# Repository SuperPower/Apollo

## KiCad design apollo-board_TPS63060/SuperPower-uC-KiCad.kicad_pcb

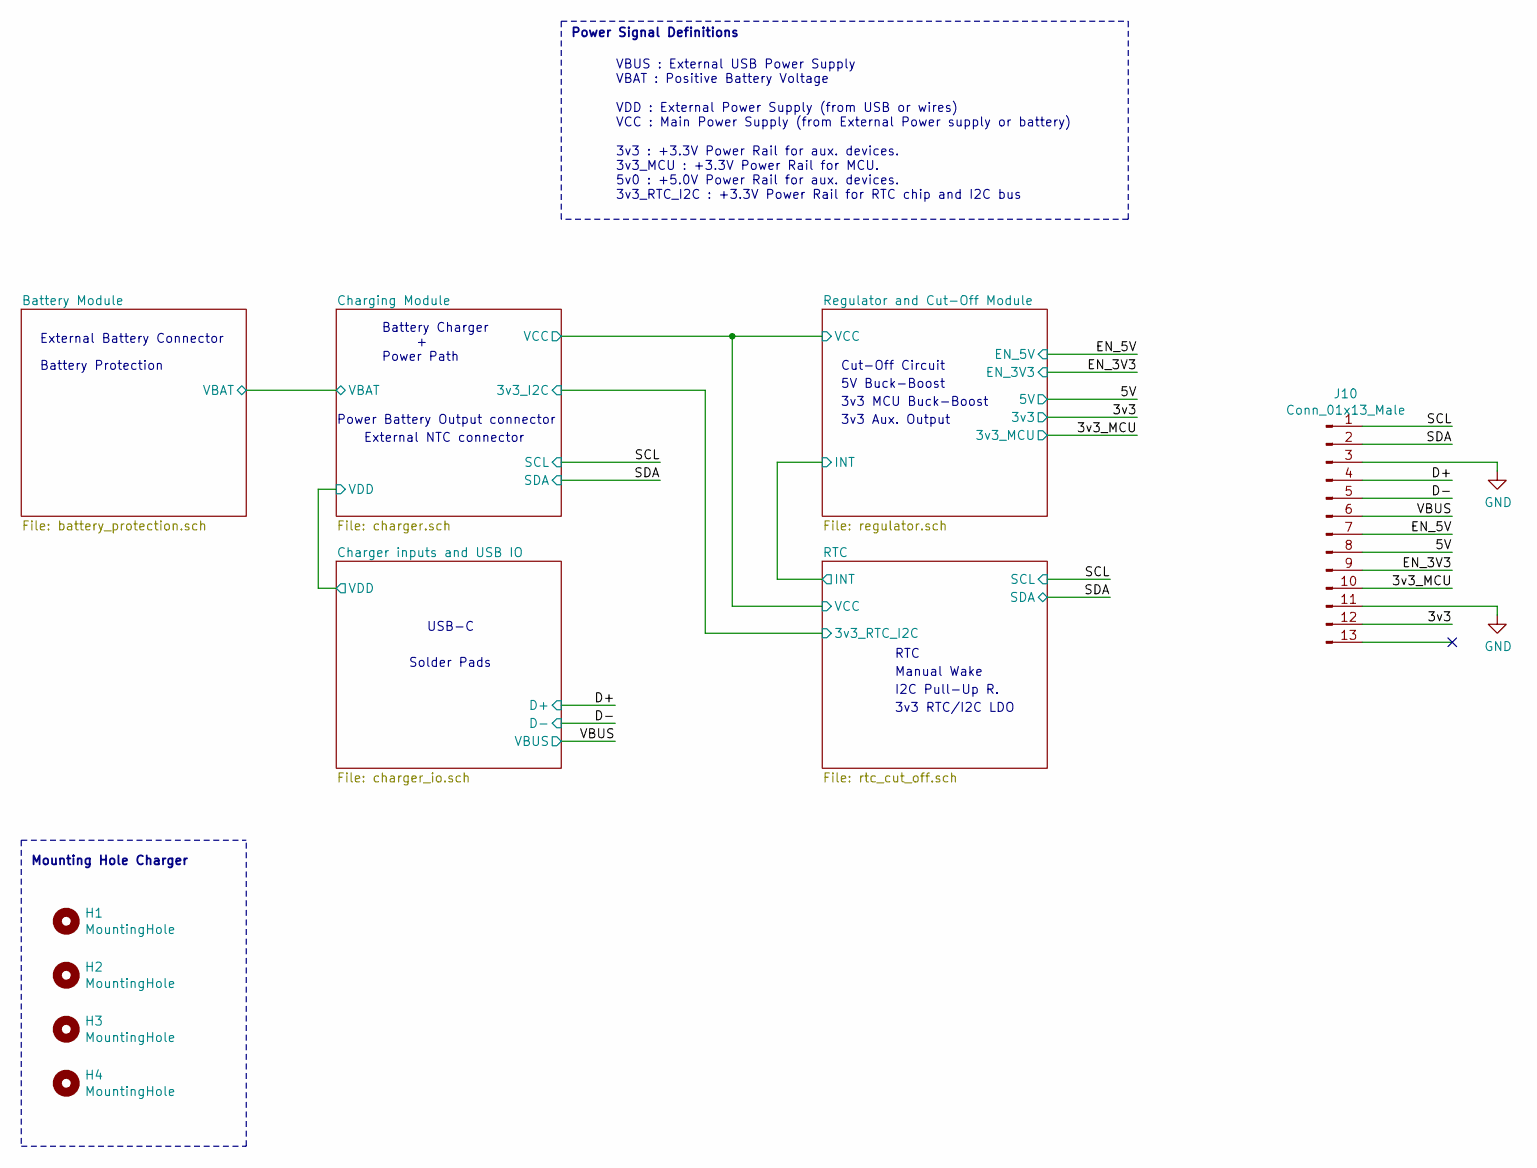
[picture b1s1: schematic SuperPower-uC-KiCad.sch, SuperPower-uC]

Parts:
H1, H2, H3, H4: MountingHole; MountingHole_2.5mm
J10: Conn_01x13_Male; PinSocket_1x13_P2.54mm_Vertical

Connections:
/3v3: J10.12; also elsewhere on the board
/3v3_MCU: J10.10; also elsewhere on the board
/5V: J10.8; also elsewhere on the board
/D+: J10.4; also elsewhere on the board
/D-: J10.5; also elsewhere on the board
/EN_3V3: J10.9; also elsewhere on the board
/EN_5V: J10.7; also elsewhere on the board
/SCL: J10.1; also elsewhere on the board
/SDA: J10.2; also elsewhere on the board
GND: J10.3, J10.11; also elsewhere on the board
VBUS: J10.6; also elsewhere on the board

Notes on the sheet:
External Battery Connector
Battery Protection
Battery Charger + Power Path
3v3 RTC/I2C LDO
3v3 MCU Buck-Boost
5V Buck-Boost
RTC
Cut-Off Circuit
USB-C
Solder Pads
Manual Wake
I2C Pull-Up R.
Mounting Hole Charger
Power Battery Output connector
External NTC connector
3v3 Aux. Output
VBUS : External USB Power Supply VBAT : Positive Battery Voltage VDD : External Power Supply (from USB or wires) VCC : Main Power Supply (from External Power supply or battery) 3v3 : +3.3V Power Rail for aux. devices. 3v3_MCU : +3.3V Power Rail for MCU. 5v0 : +5.0V Power Rail for aux. devices. 3v3_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
Power Signal Definitions

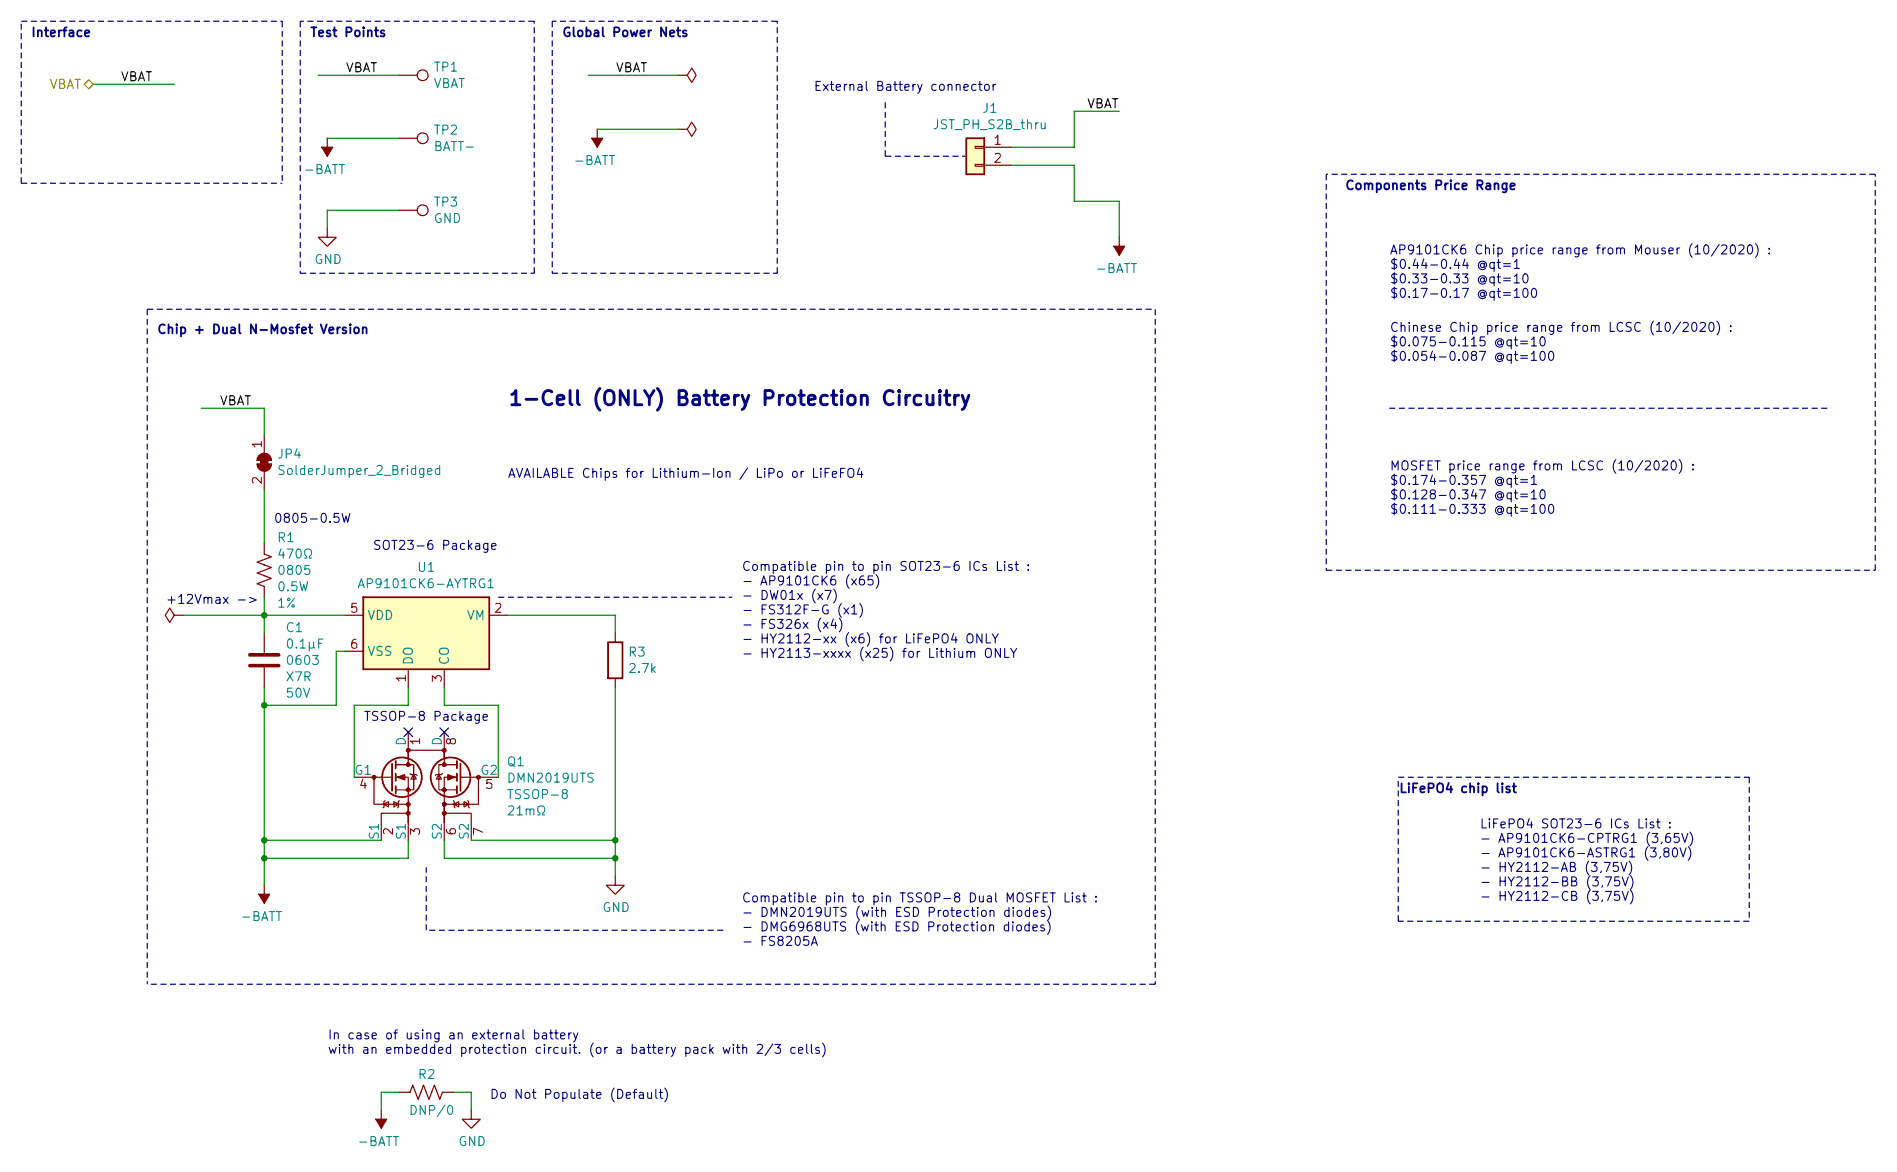
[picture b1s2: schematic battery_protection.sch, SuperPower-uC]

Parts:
C1: CC0603JRX7R9BB104; C_0603_1608Metric; Farnell_ref 3369214
J1: JST_PH_S2B_thru; JST_PH_S2B-PH-K_1x02_P2.00mm_Horizontal; Farnell_ref 9491902
JP4: SolderJumper_2_Bridged; SolderJumper-2_P1.3mm_Bridged_RoundedPad1.0x1.5mm
Q1: DMN2019UTS; TSSOP-8_4.4x3mm_P0.65mm; Farnell_check_date 2020-12-05
R1: ERJ-P06F4700V; R_0805_2012Metric; Farnell_check_date 2020-12-17
R2: DNP/0; R_0603_1608Metric
R3: 2.7k; R_0603_1608Metric
TP1: VBAT; TestPoint_Pad_D1.0mm
TP2: BATT-; TestPoint_Pad_D1.0mm
TP3: GND; TestPoint_Pad_D1.0mm
U1: AP9101CK6-AYTRG1; SOT-23-6; Farnell_check_date 2020-11-28

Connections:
-BATT: C1.2, J1.2, Q1.2 (S1), Q1.3 (S1), R2.2, TP2.1, U1.6 (VSS)
/Battery Module/VBAT: J1.1, JP4.1 (A), TP1.1; also elsewhere on the board
GND: Q1.6 (S2), Q1.7 (S2), R2.1, R3.2, TP3.1; also elsewhere on the board
unnamed: C1.1, R1.2, U1.5 (VDD)
unnamed: JP4.2 (B), R1.1
unnamed: Q1.4 (G1), U1.1 (DO)
unnamed: Q1.5 (G2), U1.3 (CO)
unnamed: R3.1, U1.2 (VM)

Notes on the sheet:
SOT23-6 Package
TSSOP-8 Package
Compatible pin to pin SOT23-6 ICs List : - AP9101CK6 (x65) - DW01x (x7) - FS312F-G (x1) - FS326x (x4) - HY2112-xx (x6) for LiFePO4 ONLY - HY2113-xxxx (x25) for Lithium ONLY
AVAILABLE Chips for Lithium-Ion / LiPo or LiFeFO4
AP9101CK6 Chip price range from Mouser (10/2020) : $0.44-0.44 @qt=1 $0.33-0.33 @qt=10 $0.17-0.17 @qt=100
Compatible pin to pin TSSOP-8 Dual MOSFET List : - DMN2019UTS (with ESD Protection diodes) - DMG6968UTS (with ESD Protection diodes) - FS8205A
MOSFET price range from LCSC (10/2020) : $0.174-0.357 @qt=1 $0.128-0.347 @qt=10 $0.111-0.333 @qt=100
LiFePO4 SOT23-6 ICs List : - AP9101CK6-CPTRG1 (3,65V) - AP9101CK6-ASTRG1 (3,80V) - HY2112-AB (3,75V) - HY2112-BB (3,75V) - HY2112-CB (3,75V)
Chinese Chip price range from LCSC (10/2020) : $0.075-0.115 @qt=10 $0.054-0.087 @qt=100
Chip + Dual N-Mosfet Version
LiFePO4 chip list
In case of using an external battery with an embedded protection circuit. (or a battery pack with 2/3 cells)
External Battery connector
Interface
Components Price Range
1-Cell (ONLY) Battery Protection Circuitry
+12Vmax ->
Do Not Populate (Default)
0805-0.5W
Test Points
Global Power Nets

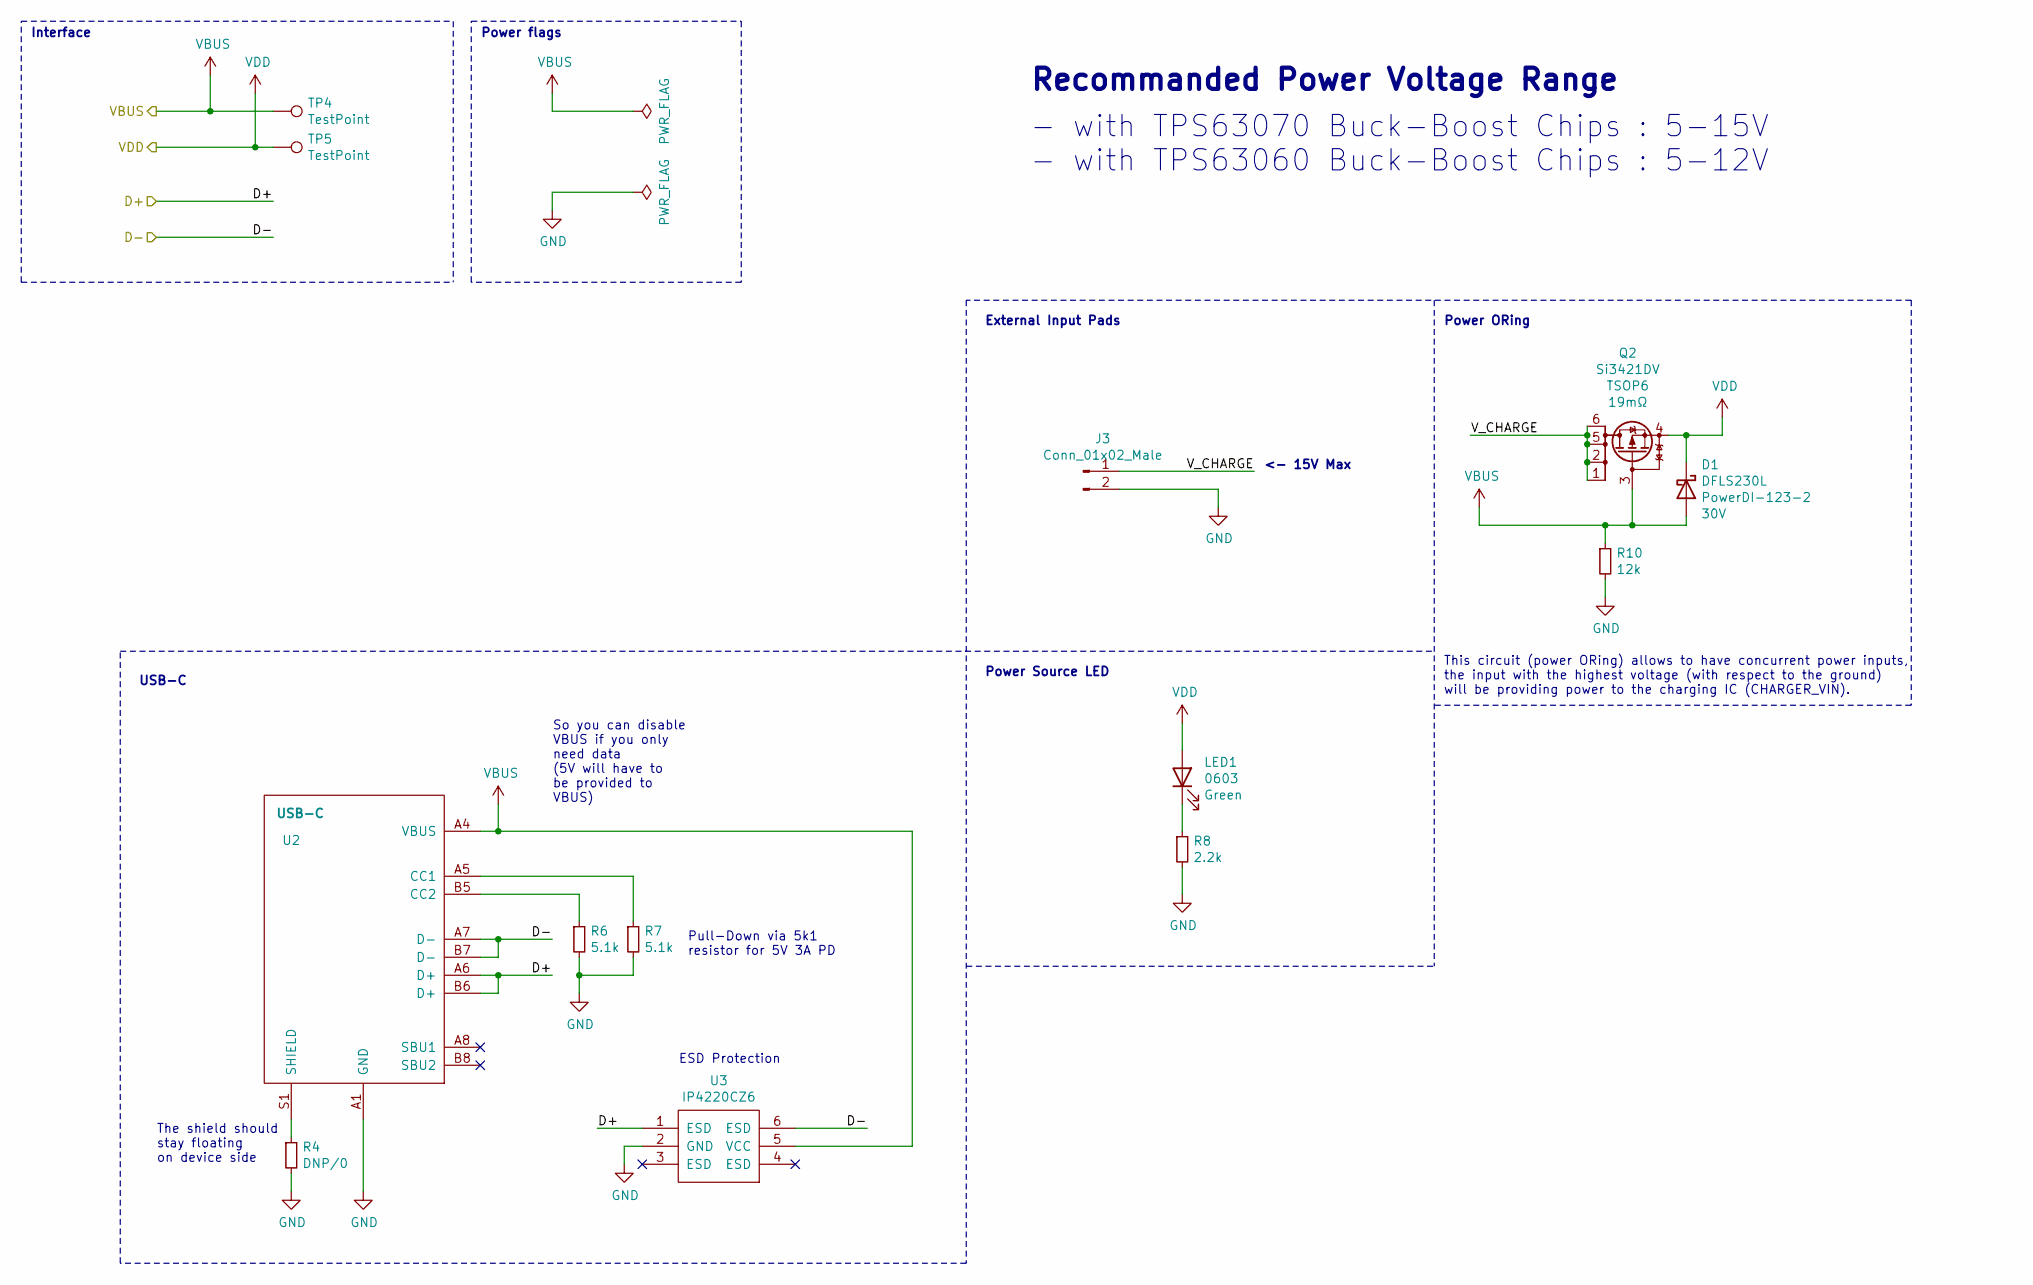
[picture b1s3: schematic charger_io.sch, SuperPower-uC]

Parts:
D1: DFLS230L; D_PowerDI-123; Farnell_ref 1858663
J3: Conn_01x02_Male; ext_input_pads
LED1: 150060VS75000_0603; LED_0603_1608Metric; Farnell_ref 2322073
Q2: Si3421DV; TSOP-6_1.65x3.05mm_P0.95mm; Farnell_ref 3405183
R4: DNP/0; R_0603_1608Metric
R6, R7: 5.1k; R_0603_1608Metric
R8: 2.2k; R_0603_1608Metric
R10: 12k; R_0603_1608Metric
TP4, TP5: TestPoint; TestPoint_Pad_D1.0mm
U2: USB-C; usb-c-usb4105
U3: IP4220CZ6; TSOP-6_1.65x3.05mm_P0.95mm

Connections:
/Charger inputs and USB IO/V_CHARGE: J3.1, Q2.1 (D), Q2.2 (D), Q2.5 (D), Q2.6 (D)
/D+: U2.A6 (D+), U2.B6 (D+), U3.1 (ESD); also elsewhere on the board
/D-: U2.A7 (D-), U2.B7 (D-), U3.6 (ESD); also elsewhere on the board
GND: J3.2, R4.2, R6.2, R7.2, R8.2, R10.2, U2.A1 (GND), U2.A12 (GND), U2.B1 (GND), U2.B12 (GND), U3.2 (GND); also elsewhere on the board
unnamed: LED1.1 (K), R8.1
unnamed: R4.1, U2.S1 (SHIELD)
unnamed: R6.1, U2.B5 (CC2)
unnamed: R7.1, U2.A5 (CC1)
VBUS: D1.2 (A), Q2.3 (G), R10.1, TP4.1, U2.A4 (VBUS), U2.A9 (VBUS), U2.B4 (VBUS), U2.B9 (VBUS), U3.5 (VCC); also elsewhere on the board
VDD: D1.1 (K), LED1.2 (A), Q2.4 (S), TP5.1; also elsewhere on the board

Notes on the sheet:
Pull-Down via 5k1 resistor for 5V 3A PD
External Input Pads
USB-C
So you can disable VBUS if you only need data (5V will have to be provided to VBUS)
ESD Protection
The shield should stay floating on device side
Power ORing
This circuit (power ORing) allows to have concurrent power inputs, the input with the highest voltage (with respect to the ground) will be providing power to the charging IC (CHARGER_VIN).
Power Source LED
Interface
Recommanded Power Voltage Range
<- 15V Max
Power flags
- with TPS63070 Buck-Boost Chips : 5-15V - with TPS63060 Buck-Boost Chips : 5-12V

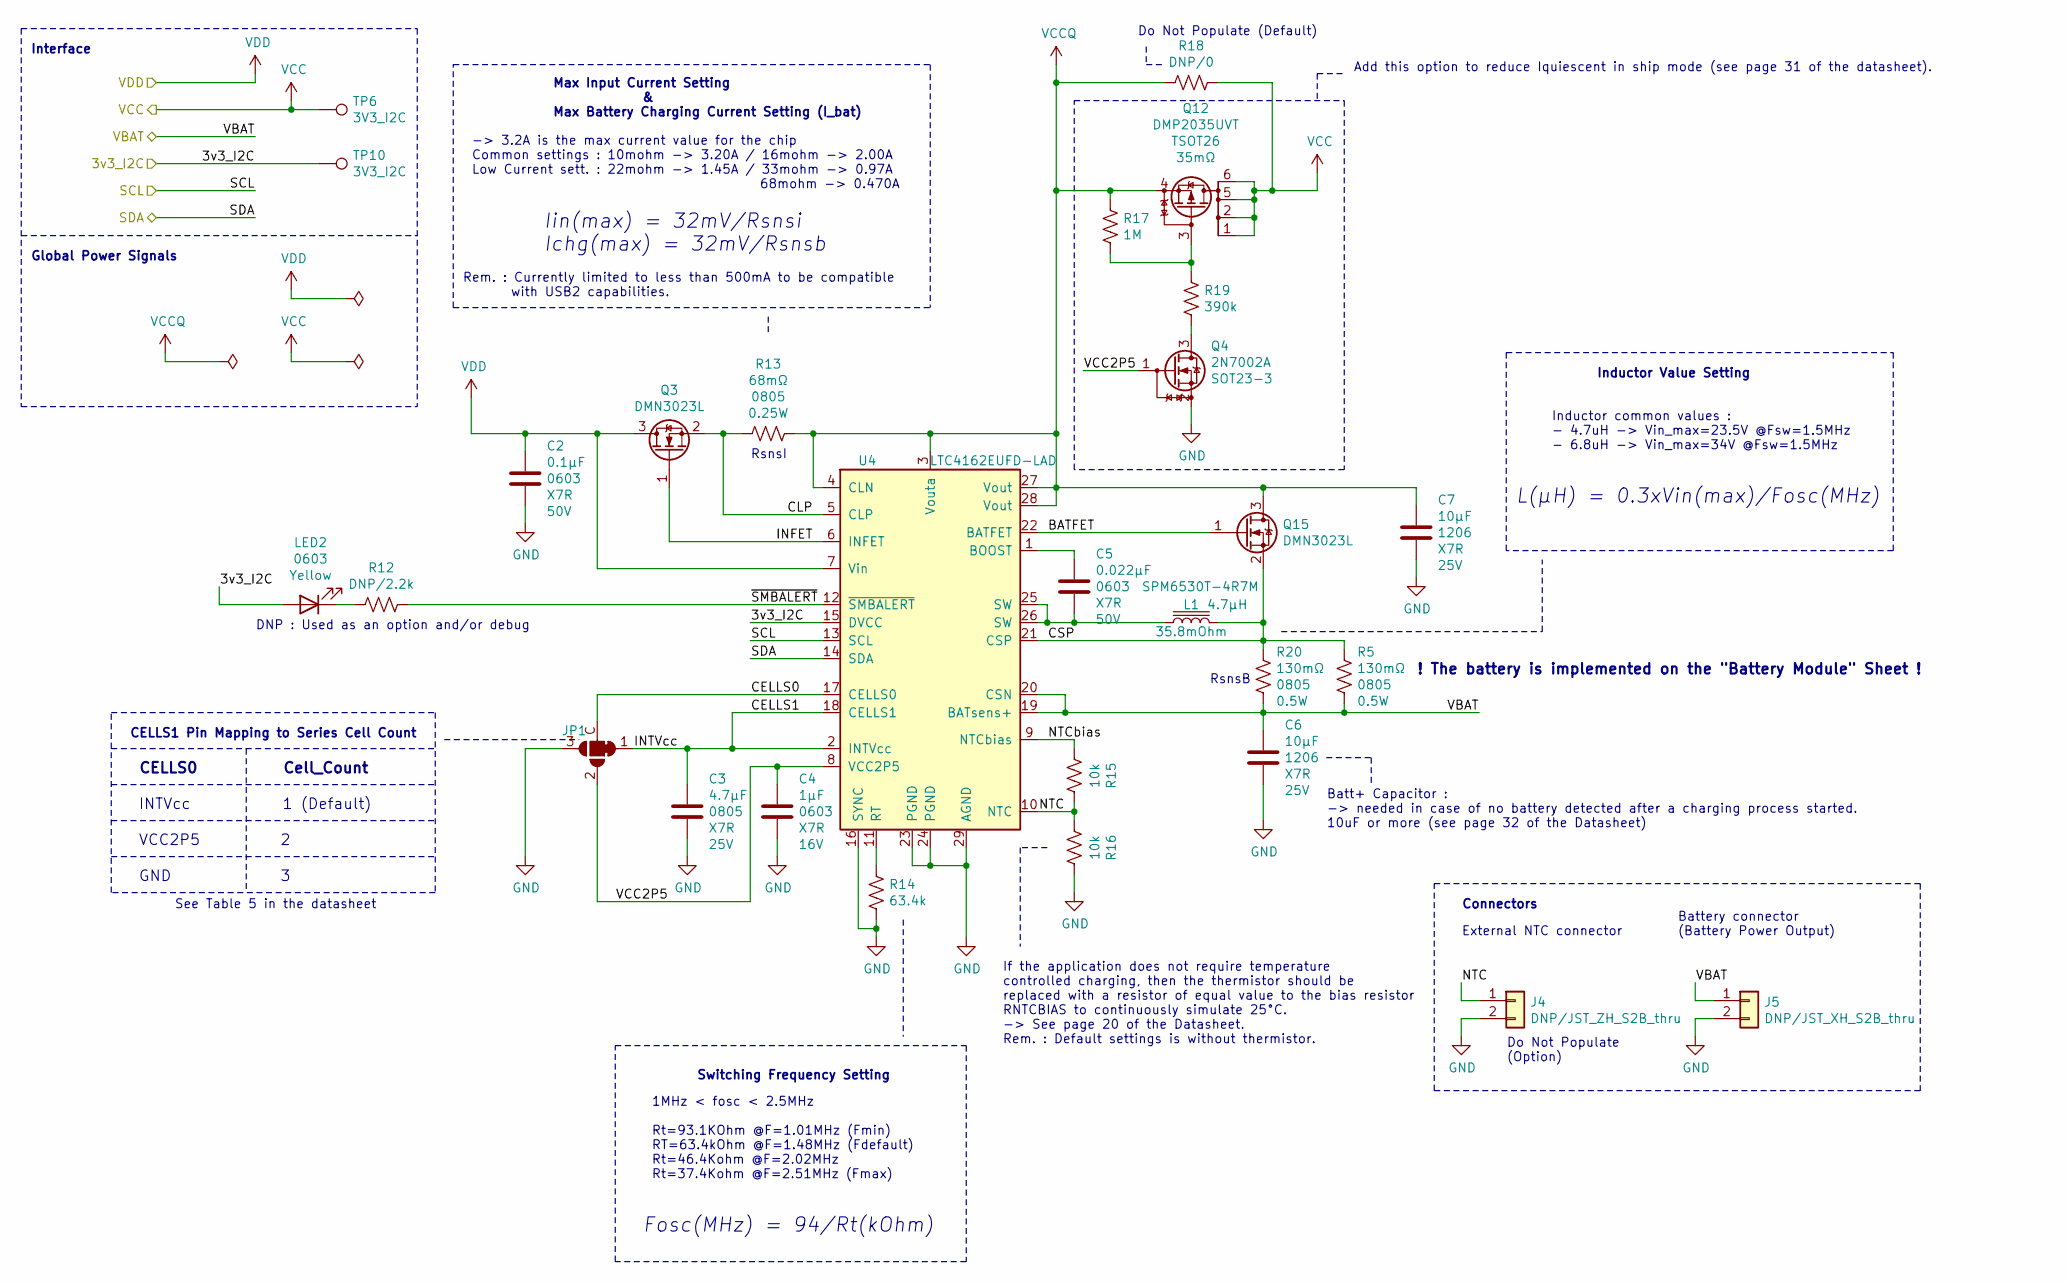
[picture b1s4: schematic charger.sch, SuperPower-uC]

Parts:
C2: CC0603JRX7R9BB104; C_0603_1608Metric; Farnell_ref 3369214
C3: TMK212AB7475KG-T; C_0805_2012Metric; Farnell_ref 2779199
C4: CL10B105KO8NNNC; C_0603_1608Metric; Farnell_ref 3013416
C5: CL10B223KB8NNNC; C_0603_1608Metric; Farnell_ref 3013425
C6, C7: CL31B106KAHNNNE; C_1206_3216Metric; Farnell_ref 3013526
J4: DNP/JST_ZH_S2B_thru; PinHeader_1x02_P1.27mm_Vertical; Farnell_ref 9491813
J5: DNP/JST_XH_S2B_thru; PinHeader_1x02_P2.54mm_Vertical; Farnell_ref 1516289
JP1: SolderJumper_4_Bridged_1C; SolderJumper-4_P2.0mm_Bridged1C_TrianglePad1.0x1.5mm_Number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
L1: SPM6530T-4R7M; L_TDK_SPM6530T; LCSC_ref C76857
LED2: 150060YS75000_0603; LED_0603_1608Metric; Farnell_ref 2322074
Q3, Q15: DMN3023L; SOT-23
Q4: 2N7002A; SOT-23; Farnell_ref 3127180
Q12: DMP2035UVT; SOT-23-6; Farnell_ref 3405183
R5, R20: ERJ-6DSFR13V; R_0805_2012Metric; Farnell_check_date 2021-08-02
R12: DNP/2.2k; R_0603_1608Metric
R13: RL0805FR-7W0R068L; R_0805_2012Metric; Farnell_ref 8067694
R14: 63.4k; R_0603_1608Metric
R15, R16: 10k; R_0603_1608Metric
R17: 1M; R_0603_1608Metric
R18: DNP/0; R_0603_1608Metric
R19: 390k; R_0603_1608Metric
TP6, TP10: 3V3_I2C; TestPoint_Pad_D1.0mm
U4: LTC4162EUFD-LAD; QFN-28-1EP_4x5mm_P0.5mm_EP2.65x3.65mm_ThermalVias; Farnell_check_date 2020-11-22

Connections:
/Battery Module/VBAT: C6.1, J5.1, R5.2, R20.2, U4.19 (BATsens+), U4.20 (CSN); also elsewhere on the board
/Charging Module/3v3_I2C: LED2.2 (A), TP10.1, U4.15 (DVCC); also elsewhere on the board
/Charging Module/BATFET: Q15.1 (G), U4.22 (BATFET)
/Charging Module/CELLS0: JP1.C (Com), U4.17 (CELLS0)
/Charging Module/CELLS1: C3.1, JP1.1 (A), U4.2 (INTVcc), U4.18 (CELLS1)
/Charging Module/CLP: Q3.2 (S), R13.2, U4.5 (CLP)
/Charging Module/CSP: L1.2, Q15.2 (S), R5.1, R20.1, U4.21 (CSP)
/Charging Module/INFET: Q3.1 (G), U4.6 (INFET)
/Charging Module/NTC: J4.1, R15.1, R16.2, U4.10 (NTC)
/Charging Module/NTCbias: R15.2, U4.9 (NTCbias)
/Charging Module/VCC2P5: C4.1, JP1.2 (B), Q4.1 (G), U4.8 (VCC2P5)
/Charging Module/~SMBALERT: R12.1, U4.12 (~SMBALERT)
/SCL: U4.13 (SCL); also elsewhere on the board
/SDA: U4.14 (SDA); also elsewhere on the board
GND: C2.2, C3.2, C4.2, C6.2, C7.2, J4.2, J5.2, JP1.3 (C), Q4.2 (S), R14.1, R16.1, U4.16 (SYNC), U4.23 (PGND), U4.24 (PGND), U4.29 (AGND); also elsewhere on the board
unnamed: C5.1, U4.1 (BOOST)
unnamed: C5.2, L1.1, U4.25 (SW), U4.26 (SW)
unnamed: LED2.1 (K), R12.2
unnamed: Q4.3 (D), R19.2
unnamed: Q12.3 (G), R17.2, R19.1
unnamed: R14.2, U4.11 (RT)
VCC: Q12.1 (D), Q12.2 (D), Q12.5 (D), Q12.6 (D), R18.1, TP6.1; also elsewhere on the board
VCCQ: C7.1, Q12.4 (S), Q15.3 (D), R13.1, R17.1, R18.2, U4.3 (Vouta), U4.4 (CLN), U4.27 (Vout), U4.28 (Vout)
VDD: C2.1, Q3.3 (D), U4.7 (Vin); also elsewhere on the board

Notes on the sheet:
RsnsB
RsnsI
If the application does not require temperature controlled charging, then the thermistor should be replaced with a resistor of equal value to the bias resistor RNTCBIAS to continuously simulate 25°C. -> See page 20 of the Datasheet. Rem. : Default settings is without thermistor.
Batt+ Capacitor : -> needed in case of no battery detected after a charging process started. 10uF or more (see page 32 of the Datasheet)
1MHz < fosc < 2.5MHz Rt=93.1KOhm @F=1.01MHz (Fmin) RT=63.4kOhm @F=1.48MHz (Fdefault) Rt=46.4Kohm @F=2.02MHz Rt=37.4Kohm @F=2.51MHz (Fmax)
Inductor common values : - 4.7uH -> Vin_max=23.5V @Fsw=1.5MHz - 6.8uH -> Vin_max=34V @Fsw=1.5MHz
Add this option to reduce Iquiescent in ship mode (see page 31 of the datasheet).
External NTC connector
Switching Frequency Setting
Max Input Current Setting & Max Battery Charging Current Setting (I_bat)
-> 3.2A is the max current value for the chip Common settings : 10mohm -> 3.20A / 16mohm -> 2.00A Low Current sett. : 22mohm -> 1.45A / 33mohm -> 0.97A 68mohm -> 0.470A
Inductor Value Setting
Battery connector (Battery Power Output)
DNP : Used as an option and/or debug
See Table 5 in the datasheet
Connectors
! The battery is implemented on the "Battery Module" Sheet !
Iin(max) = 32mV/Rsnsi Ichg(max) = 32mV/Rsnsb
Fosc(MHz) = 94/Rt(kOhm)
L(µH) = 0.3xVin(max)/Fosc(MHz)
CELLS1 Pin Mapping to Series Cell Count
CELLS0
Cell_Count
INTVcc
VCC2P5
GND
1 (Default)
Rem. : Currently limited to less than 500mA to be compatible with USB2 capabilities.
Interface
Do Not Populate (Option)
Do Not Populate (Default)
Global Power Signals

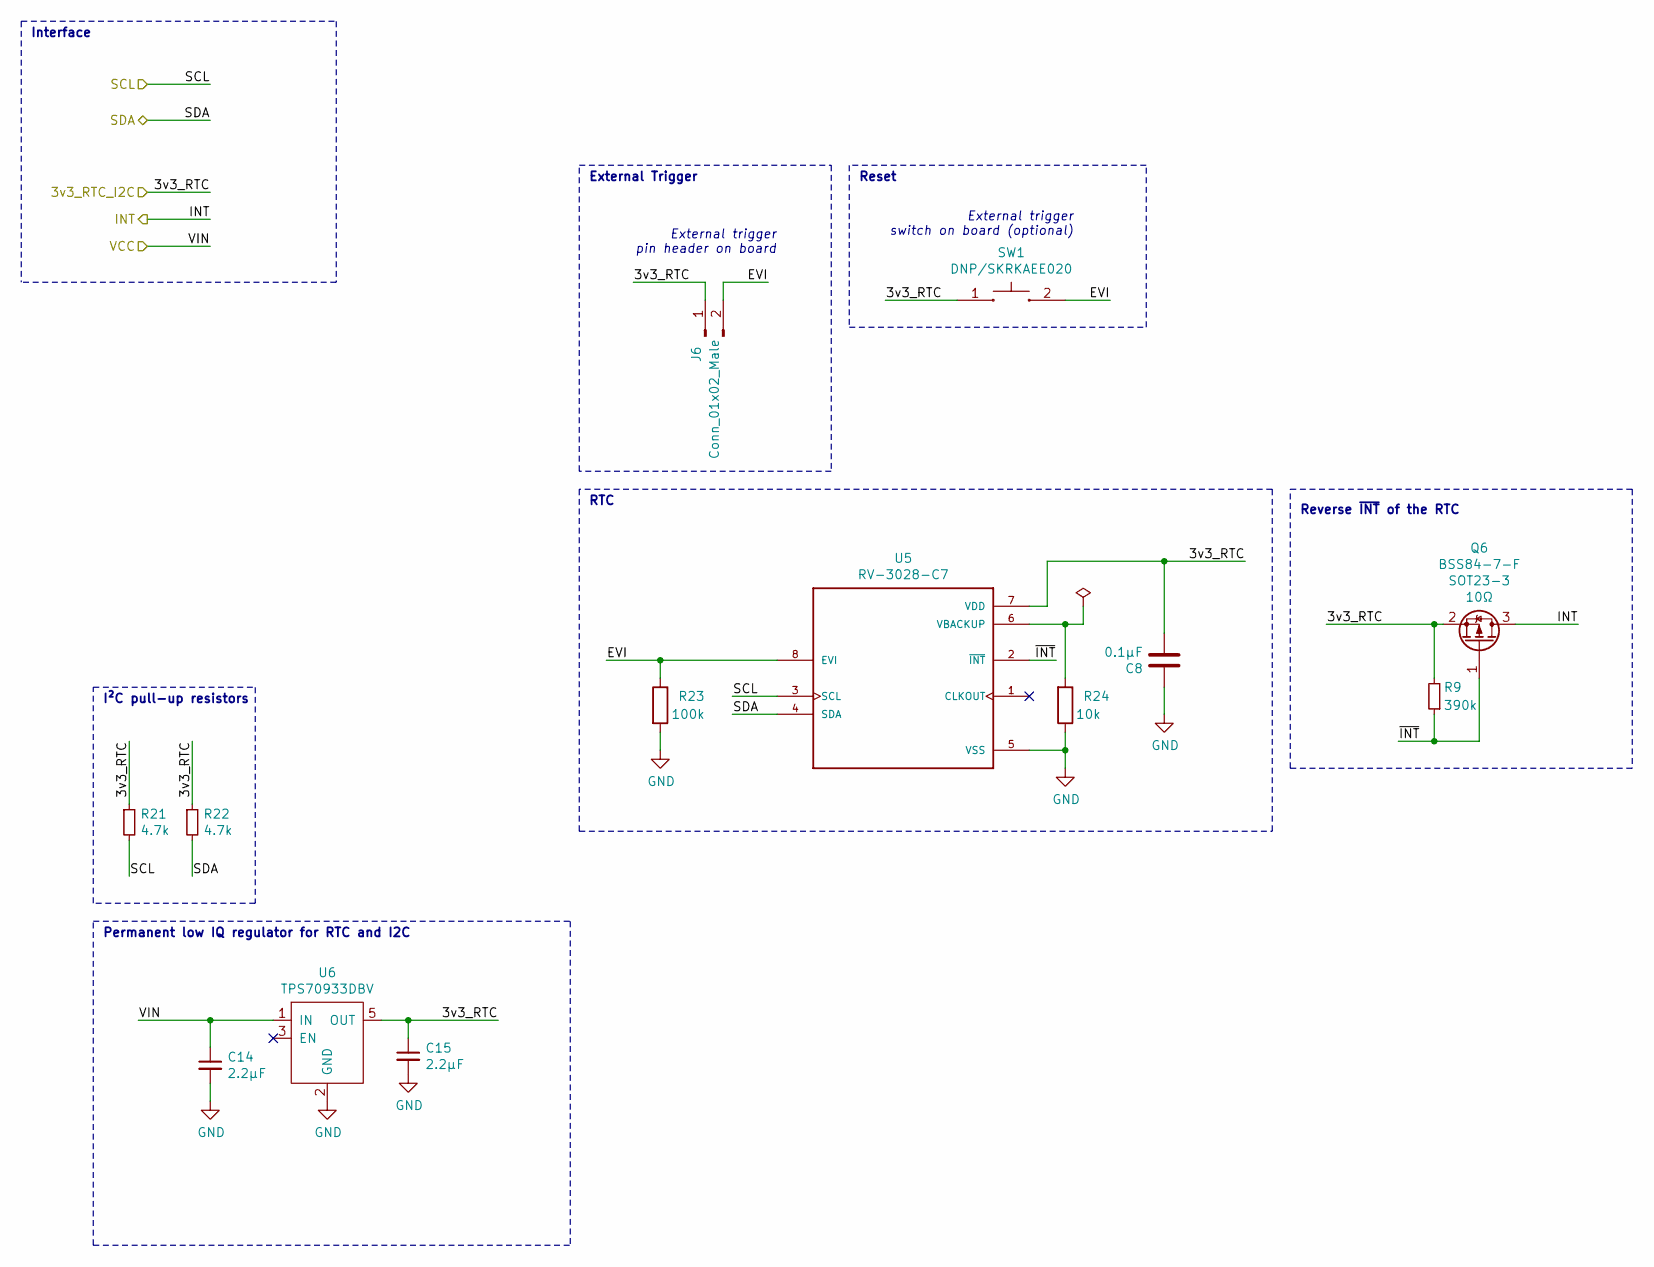
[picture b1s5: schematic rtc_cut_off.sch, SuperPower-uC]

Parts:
C8: 0.1µF; C_0603_1608Metric
C14, C15: 2.2μF; C_0603_1608Metric
J6: Conn_01x02_Male; PinSocket_1x02_P2.54mm_Vertical
Q6: BSS84-7-F; SOT-23; Farnell_ref 1843716
R9: 390k; R_0603_1608Metric
R21, R22: 4.7k; R_0603_1608Metric
R23: 100k; R_0603_1608Metric
R24: 10k; R_0603_1608Metric
SW1: DNP/SKRKAEE020; SKRKAEE020
U5: RV-3028-C7; IC_RV-3028-C7
U6: TPS70933DBV; SOT-23-5

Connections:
/Charging Module/3v3_I2C: C8.2, C15.1, J6.1, Q6.2 (S), R9.2, R21.1, R22.1, SW1.1, U5.7 (VDD), U6.5 (OUT); also elsewhere on the board
/RTC/EVI: J6.2, R23.1, SW1.2, U5.8 (EVI)
/RTC/INT: Q6.3 (D); also elsewhere on the board
/RTC/~INT: Q6.1 (G), R9.1, U5.2 (~INT~)
/SCL: R21.2, U5.3 (SCL); also elsewhere on the board
/SDA: R22.2, U5.4 (SDA); also elsewhere on the board
GND: C8.1, C14.2, C15.2, R23.2, R24.1, U5.5 (VSS), U6.2 (GND); also elsewhere on the board
unnamed: R24.2, U5.6 (VBACKUP)
VCC: C14.1, U6.1 (IN); also elsewhere on the board

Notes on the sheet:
I²C pull-up resistors
External trigger pin header on board
Interface
External trigger switch on board (optional)
RTC
Reset
External Trigger
Reverse ~INT~ of the RTC
Permanent low IQ regulator for RTC and I2C

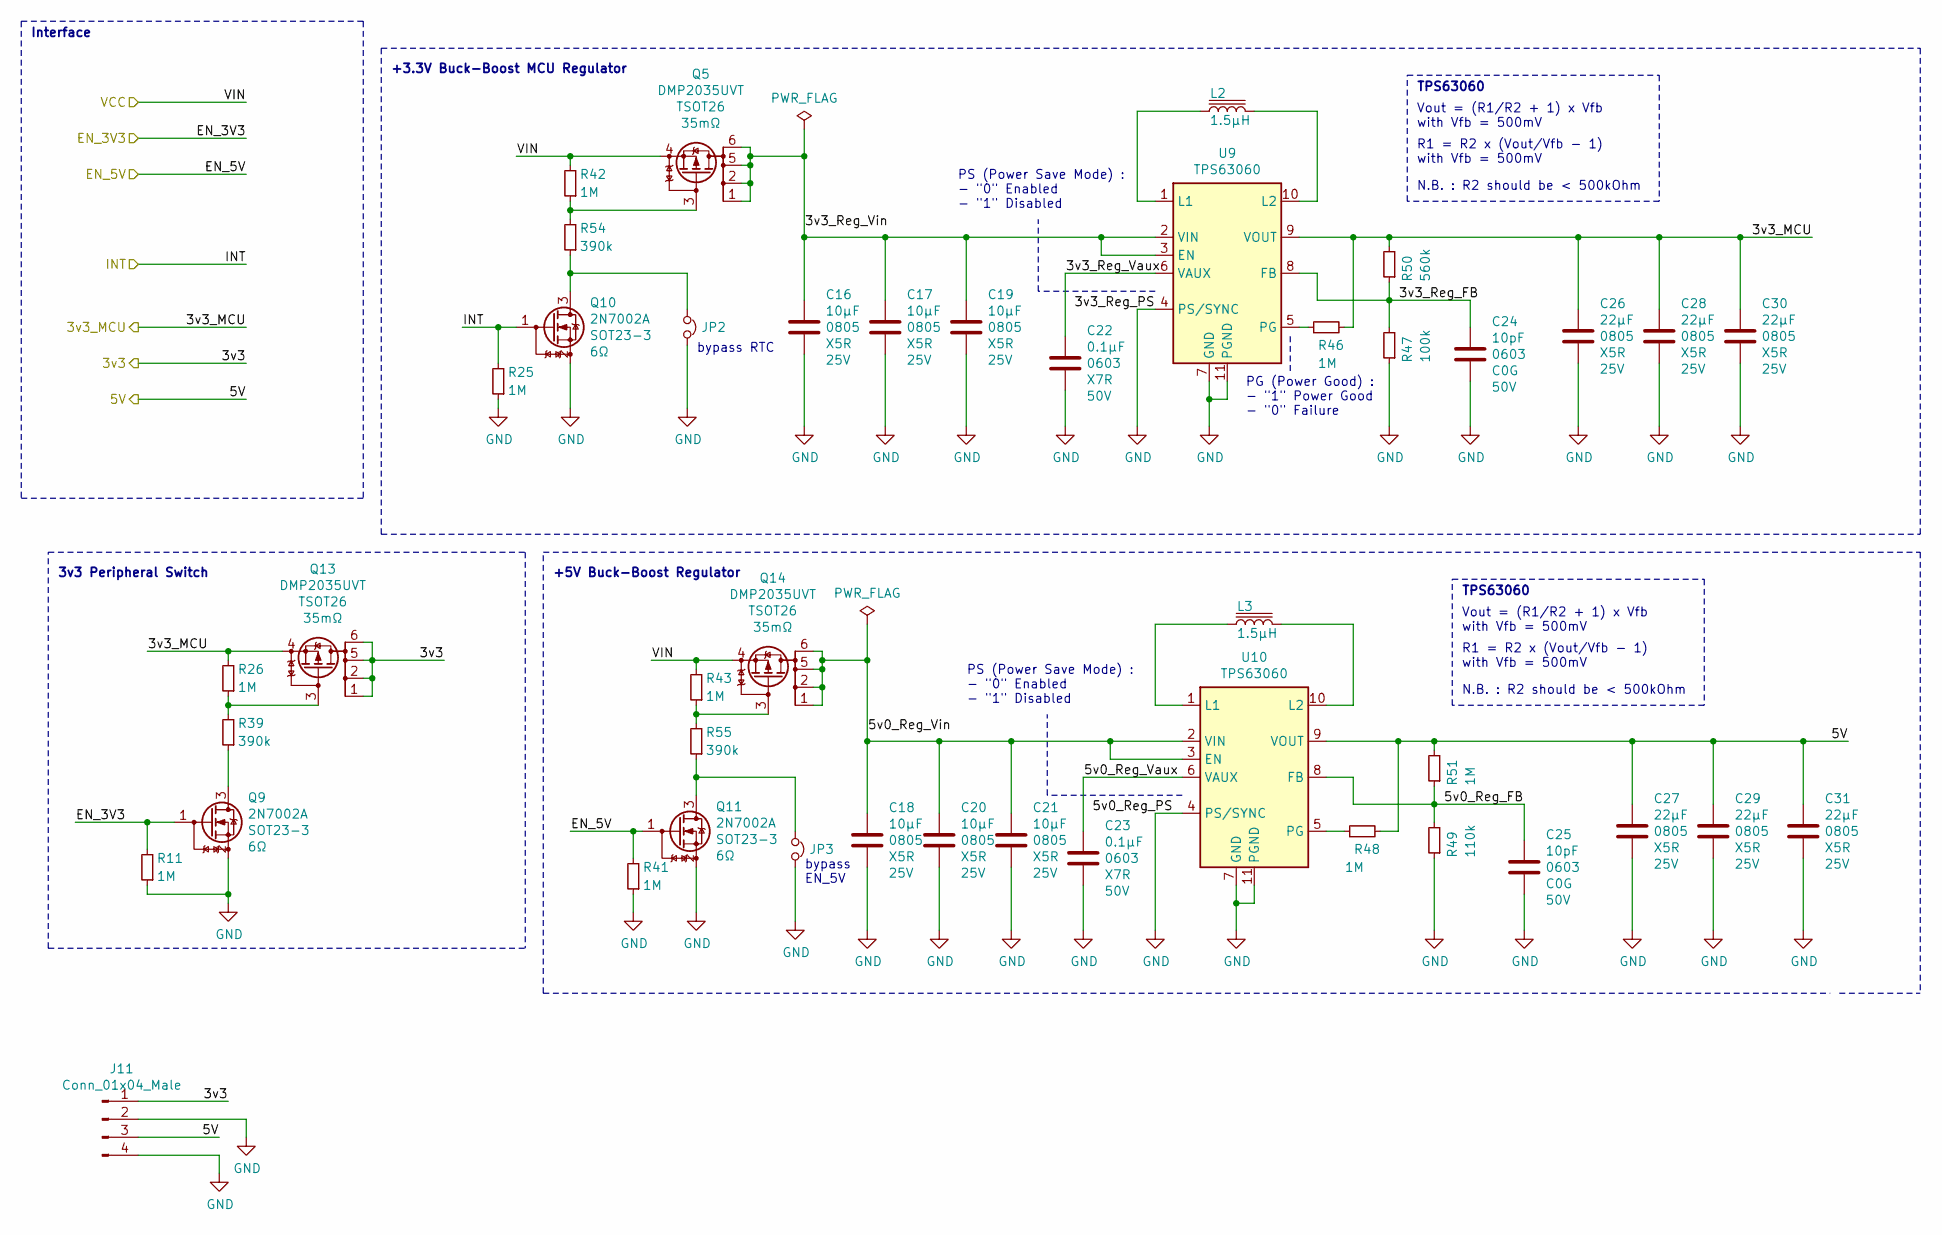
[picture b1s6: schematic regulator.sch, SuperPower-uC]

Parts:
C16, C17, C18, C19, C20, C21: CL21A106KAYNNNE; C_0805_2012Metric; Farnell_ref 3013452
C22, C23: CL10B104KB8NNNC; C_0603_1608Metric; Farnell_check_date 2021-02-23
C24, C25: CC0603JRNPO9BN100; C_0603_1608Metric; Farnell_ref 721967
C26, C27, C28, C29, C30, C31: CL21A226MAQNNNE; C_0805_2012Metric; Farnell_ref 3013459
J11: Conn_01x04_Male; PinSocket_1x04_P2.54mm_Vertical
JP2: Jumper_NC_Small; PinSocket_1x02_P2.54mm_Vertical
JP3: Jumper_NC_Small; SolderJumper-2_P1.3mm_Open_TrianglePad1.0x1.5mm
L2, L3: SPM6530T-1R5M; L_TDK_SPM6530T; Farnell_ref 2215610
Q5, Q13, Q14: DMP2035UVT; SOT-23-6; Farnell_ref 3405183
Q9, Q10, Q11: 2N7002A; SOT-23; Farnell_ref 3127180
R11, R25, R26, R41, R42, R43, R46, R48, R51: 1M; R_0603_1608Metric
R39, R54, R55: 390k; R_0603_1608Metric
R47: 100k; R_0603_1608Metric
R49: 110k; R_0603_1608Metric
R50: 560k; R_0603_1608Metric
U9, U10: TPS63060; Texas_S-PWSON-N10_ThermalVias_NSM_vias_bottom

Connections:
/3v3: J11.1, Q13.1 (D), Q13.2 (D), Q13.5 (D), Q13.6 (D); also elsewhere on the board
/3v3_MCU: C26.1, C28.1, C30.1, Q13.4 (S), R26.2, R46.2, R50.2, U9.9 (VOUT); also elsewhere on the board
/5V: C27.1, C29.1, C31.1, J11.3, R48.2, R51.2, U10.9 (VOUT); also elsewhere on the board
/EN_3V3: Q9.1 (G), R11.2; also elsewhere on the board
/EN_5V: Q11.1 (G), R41.2; also elsewhere on the board
/RTC/INT: Q10.1 (G), R25.2; also elsewhere on the board
/Regulator and Cut-Off Module/3v3_Reg_FB: C24.1, R47.2, R50.1, U9.8 (FB)
/Regulator and Cut-Off Module/3v3_Reg_Vaux: C22.1, U9.6 (VAUX)
/Regulator and Cut-Off Module/3v3_Reg_Vin: C16.1, C17.1, C19.1, Q5.1 (D), Q5.2 (D), Q5.5 (D), Q5.6 (D), U9.2 (VIN), U9.3 (EN)
/Regulator and Cut-Off Module/5v0_Reg_FB: C25.1, R49.2, R51.1, U10.8 (FB)
/Regulator and Cut-Off Module/5v0_Reg_Vaux: C23.1, U10.6 (VAUX)
/Regulator and Cut-Off Module/5v0_Reg_Vin: C18.1, C20.1, C21.1, Q14.1 (D), Q14.2 (D), Q14.5 (D), Q14.6 (D), U10.2 (VIN), U10.3 (EN)
GND: C16.2, C17.2, C18.2, C19.2, C20.2, C21.2, C22.2, C23.2, C24.2, C25.2, C26.2, C27.2, C28.2, C29.2, C30.2, C31.2, J11.2, J11.4, JP2.2, JP3.2, Q9.2 (S), Q10.2 (S), Q11.2 (S), R11.1, R25.1, R41.1, R47.1, R49.1, U9.4 (PS/SYNC), U9.7 (GND), U9.11 (PGND), U10.4 (PS/SYNC), U10.7 (GND), U10.11 (PGND); also elsewhere on the board
unnamed: JP2.1, Q10.3 (D), R54.1
unnamed: JP3.1, Q11.3 (D), R55.1
unnamed: L2.1, U9.1 (L1)
unnamed: L2.2, U9.10 (L2)
unnamed: L3.1, U10.1 (L1)
unnamed: L3.2, U10.10 (L2)
unnamed: Q5.3 (G), R42.1, R54.2
unnamed: Q9.3 (D), R39.1
unnamed: Q13.3 (G), R26.1, R39.2
unnamed: Q14.3 (G), R43.1, R55.2
unnamed: R46.1, U9.5 (PG)
unnamed: R48.1, U10.5 (PG)
VCC: Q5.4 (S), Q14.4 (S), R42.2, R43.2; also elsewhere on the board

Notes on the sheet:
Interface
+5V Buck-Boost Regulator
bypass EN_5V
bypass RTC
+3.3V Buck-Boost MCU Regulator
3v3 Peripheral Switch
PS (Power Save Mode) : - "0" Enabled - "1" Disabled
PG (Power Good) : - "1" Power Good - "0" Failure
Vout = (R1/R2 + 1) x Vfb with Vfb = 500mV
N.B. : R2 should be < 500kOhm
R1 = R2 x (Vout/Vfb - 1) with Vfb = 500mV
TPS63060

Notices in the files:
apollo-board/battery_protection.sch:
Licence: CERN-OHL-W
